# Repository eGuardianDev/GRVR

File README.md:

<div align="center" display="inline">
  <h1>Gyroscope Tracking (in) Virtual Reality</h1>

<h3>This project allows you to track points in 3d invieroment using gyroscopes.</h3>

<h4>This gives you the ability you to track your body. Uses can be found in VR Gaming, AR interfaces, sport and physical tracking, Location estimation
</h4>
</div>

<br/>
<h2>Current State:</h2>

- [X] Point localization algorithm 
- [X] API implementation
- [X] Custom json file on configuration
- [X] ESP-NOW Communication
- [ ] Controllers
- [ ] Movement algorithm
- [ ] Headset display

<h2> Tech Stack </h2>

||Hardware|Software|Additional|
|:---:|:---:|:---:|:---:|
||ESP8266|AvaloniaUI|SteamVR|
||MPU6050| |Panda3d|
||C++| C#| C++ & Python|

## Documentation

[Documentation](https://github.com/eGuardianDev/GRVR/wiki)

## Limitations
#### 1. Many sensors are needed to track every main point of the body.
#### 2. Every point should have a "parent" point. (Except point zero)

## Pictures

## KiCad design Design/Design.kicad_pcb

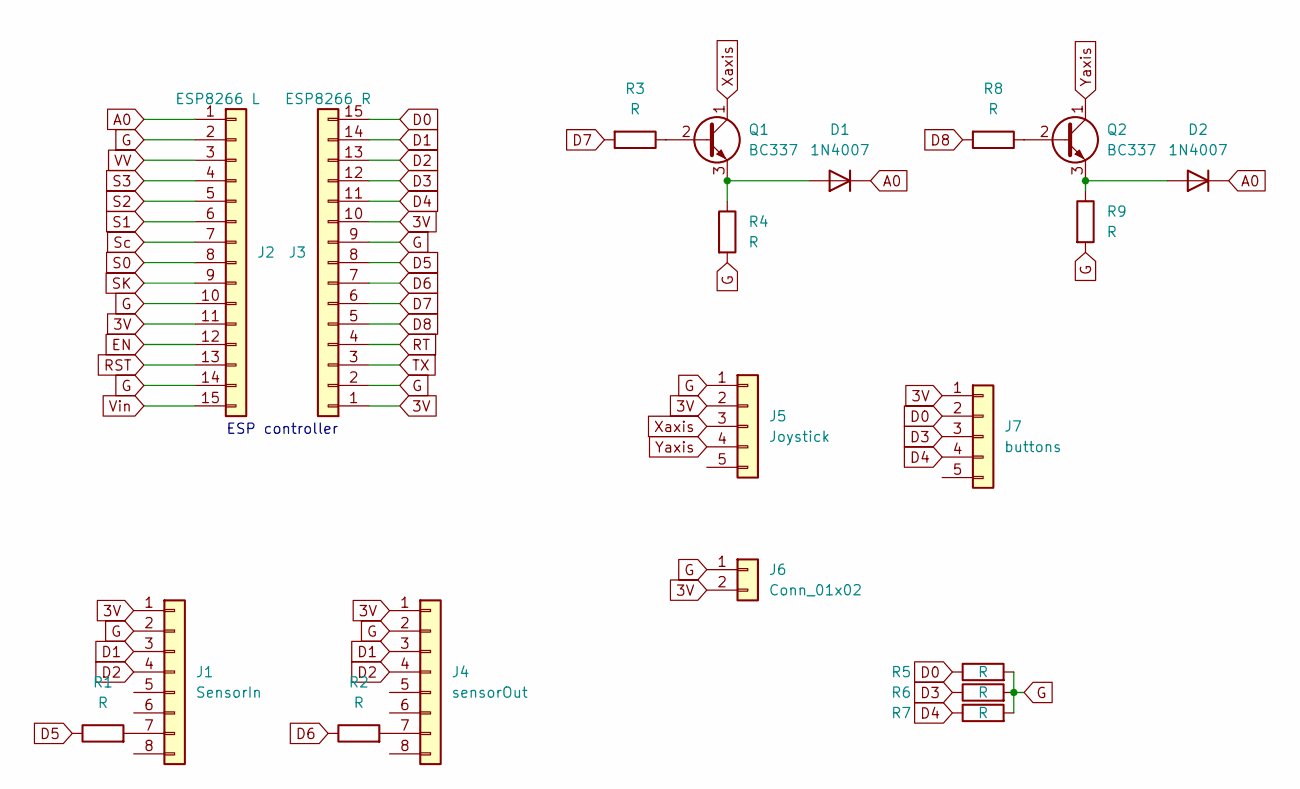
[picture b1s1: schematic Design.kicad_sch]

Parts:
D1, D2: 1N4007; D_DO-41_SOD81_P10.16mm_Horizontal
J1: SensorIn
J2: ESP8266 L; PinHeader_1x15_P2.54mm_Vertical
J3: ESP8266 R; PinHeader_1x15_P2.54mm_Vertical
J4: sensorOut; PinHeader_1x08_P2.54mm_Vertical
J5: Joystick
J6: Conn_01x02
J7: buttons; PinHeader_1x05_P2.54mm_Vertical
Q1, Q2: BC337; TO-92_Inline
R1: R
R2, R3, R4, R5, R6, R7, R8, R9: R; R_Axial_DIN0204_L3.6mm_D1.6mm_P7.62mm_Horizontal

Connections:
3V: J1.1, J2.11, J3.1, J3.10, J4.1, J5.2, J6.2, J7.1
A0: D1.1 (K), D2.1 (K), J2.1
D0: J3.15, J7.2, R5.1
D1: J1.3, J3.14, J4.3
D2: J1.4, J3.13, J4.4
D3: J3.12, J7.3, R6.1
D4: J3.11, J7.4, R7.1
D5: J3.8, R1.1
D6: J3.7, R2.1
D7: J3.6, R3.2
D8: J3.5, R8.2
EN: J2.12
G: J1.2, J2.2, J2.10, J2.14, J3.2, J3.9, J4.2, J5.1, J6.1, R4.2, R5.2, R6.2, R7.2, R9.2
unnamed: D1.2 (A), Q1.3 (E), R4.1
unnamed: D2.2 (A), Q2.3 (E), R9.1
unnamed: J1.7, R1.2
unnamed: J4.7, R2.2
unnamed: Q1.2 (B), R3.1
unnamed: Q2.2 (B), R8.1
RST: J2.13
RT: J3.4
S0: J2.8
S1: J2.6
S2: J2.5
S3: J2.4
SK: J2.9
Sc: J2.7
TX: J3.3
VV: J2.3
Vin: J2.15
Xaxis: J5.3, Q1.1 (C)
Yaxis: J5.4, Q2.1 (C)

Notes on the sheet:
ESP controller

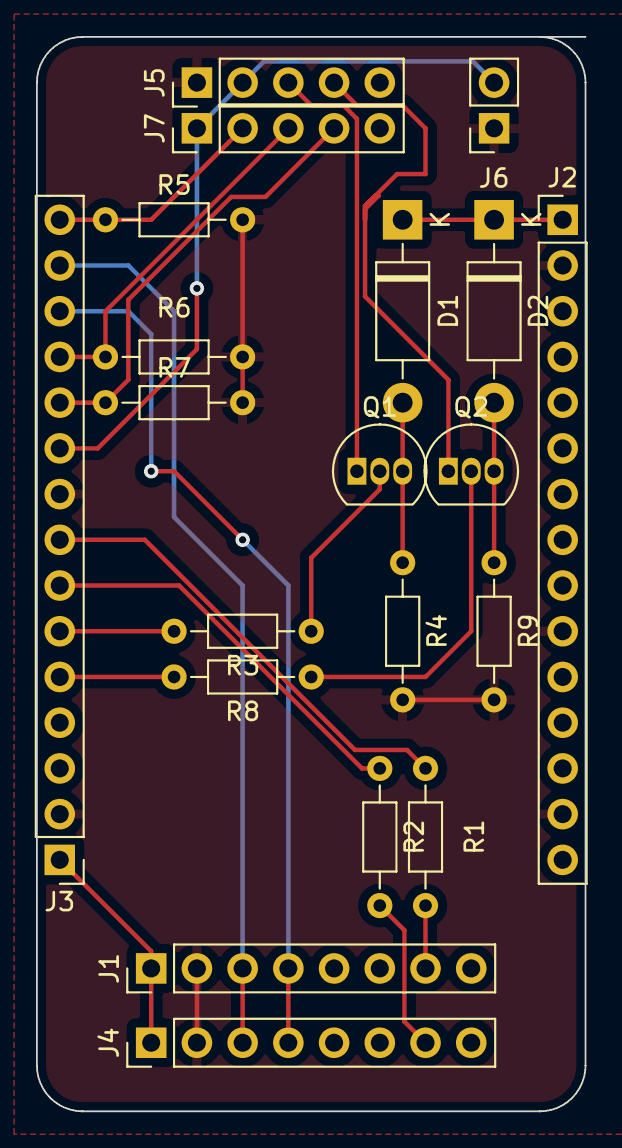
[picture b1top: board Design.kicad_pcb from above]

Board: 2 copper layers, 30.5 x 59.7 mm, 20 parts (0 on the bottom side), 20 nets.

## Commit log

2022-11-05 Firmware added
2022-11-06 adding firmware start
2022-11-06 .gitignore
2022-11-06 Tests of .gitignore
2022-11-06 idk anymore
2022-11-06 Finished firmware yay
2022-11-06 Adding this
2022-11-10 3D design and gitignore for vs 2022
2022-11-10 UI tests and this is going to be a problem
2022-11-10 some updates | binding label doesnt work
2022-11-13 idk what i did, i wrote this 2 days ago
2022-11-13 ore stuff
2022-11-14 File organization + V0.2 of desing
2022-11-14 getting software ready strcutre ready + some file renaems
2022-11-21 seria comm tests + ALGORITHMS test
2022-11-22 It's 12:47 and i wanna sleep. finaly fixed displaying the sensros and connecting the sensors, firmware almost ready
2022-11-23 making backup, before everythings explodes and catches on fire
2022-11-26 Some changes idk
2022-11-27 algorithm is finally realy ( or i hope so)
2022-12-07 index.html
2022-12-07 Test
2022-12-07 Template
2022-12-15 my sensor died. Sad. This code for the main program isn't complate and there isn't any calibration. I wasn't able to test it, becuase my sensorjust stoped working.
2022-12-30 backup
2023-01-03 changing look
    + tech stack table
    + link for docs
2023-01-03 foundations of main page
2023-01-04 New structure of website
2023-01-09 pcb design
2023-01-15 general changes
2023-01-31 This is a problem. I did some changes here but this is the site branch
2023-01-31 New changes and structure
2023-02-17 TOO MANY CHANGES
2023-02-28 Some information updates
    Better structure of text and fixing some problems
2023-03-15 Design changes and structure
2025-02-06 Some pictures
